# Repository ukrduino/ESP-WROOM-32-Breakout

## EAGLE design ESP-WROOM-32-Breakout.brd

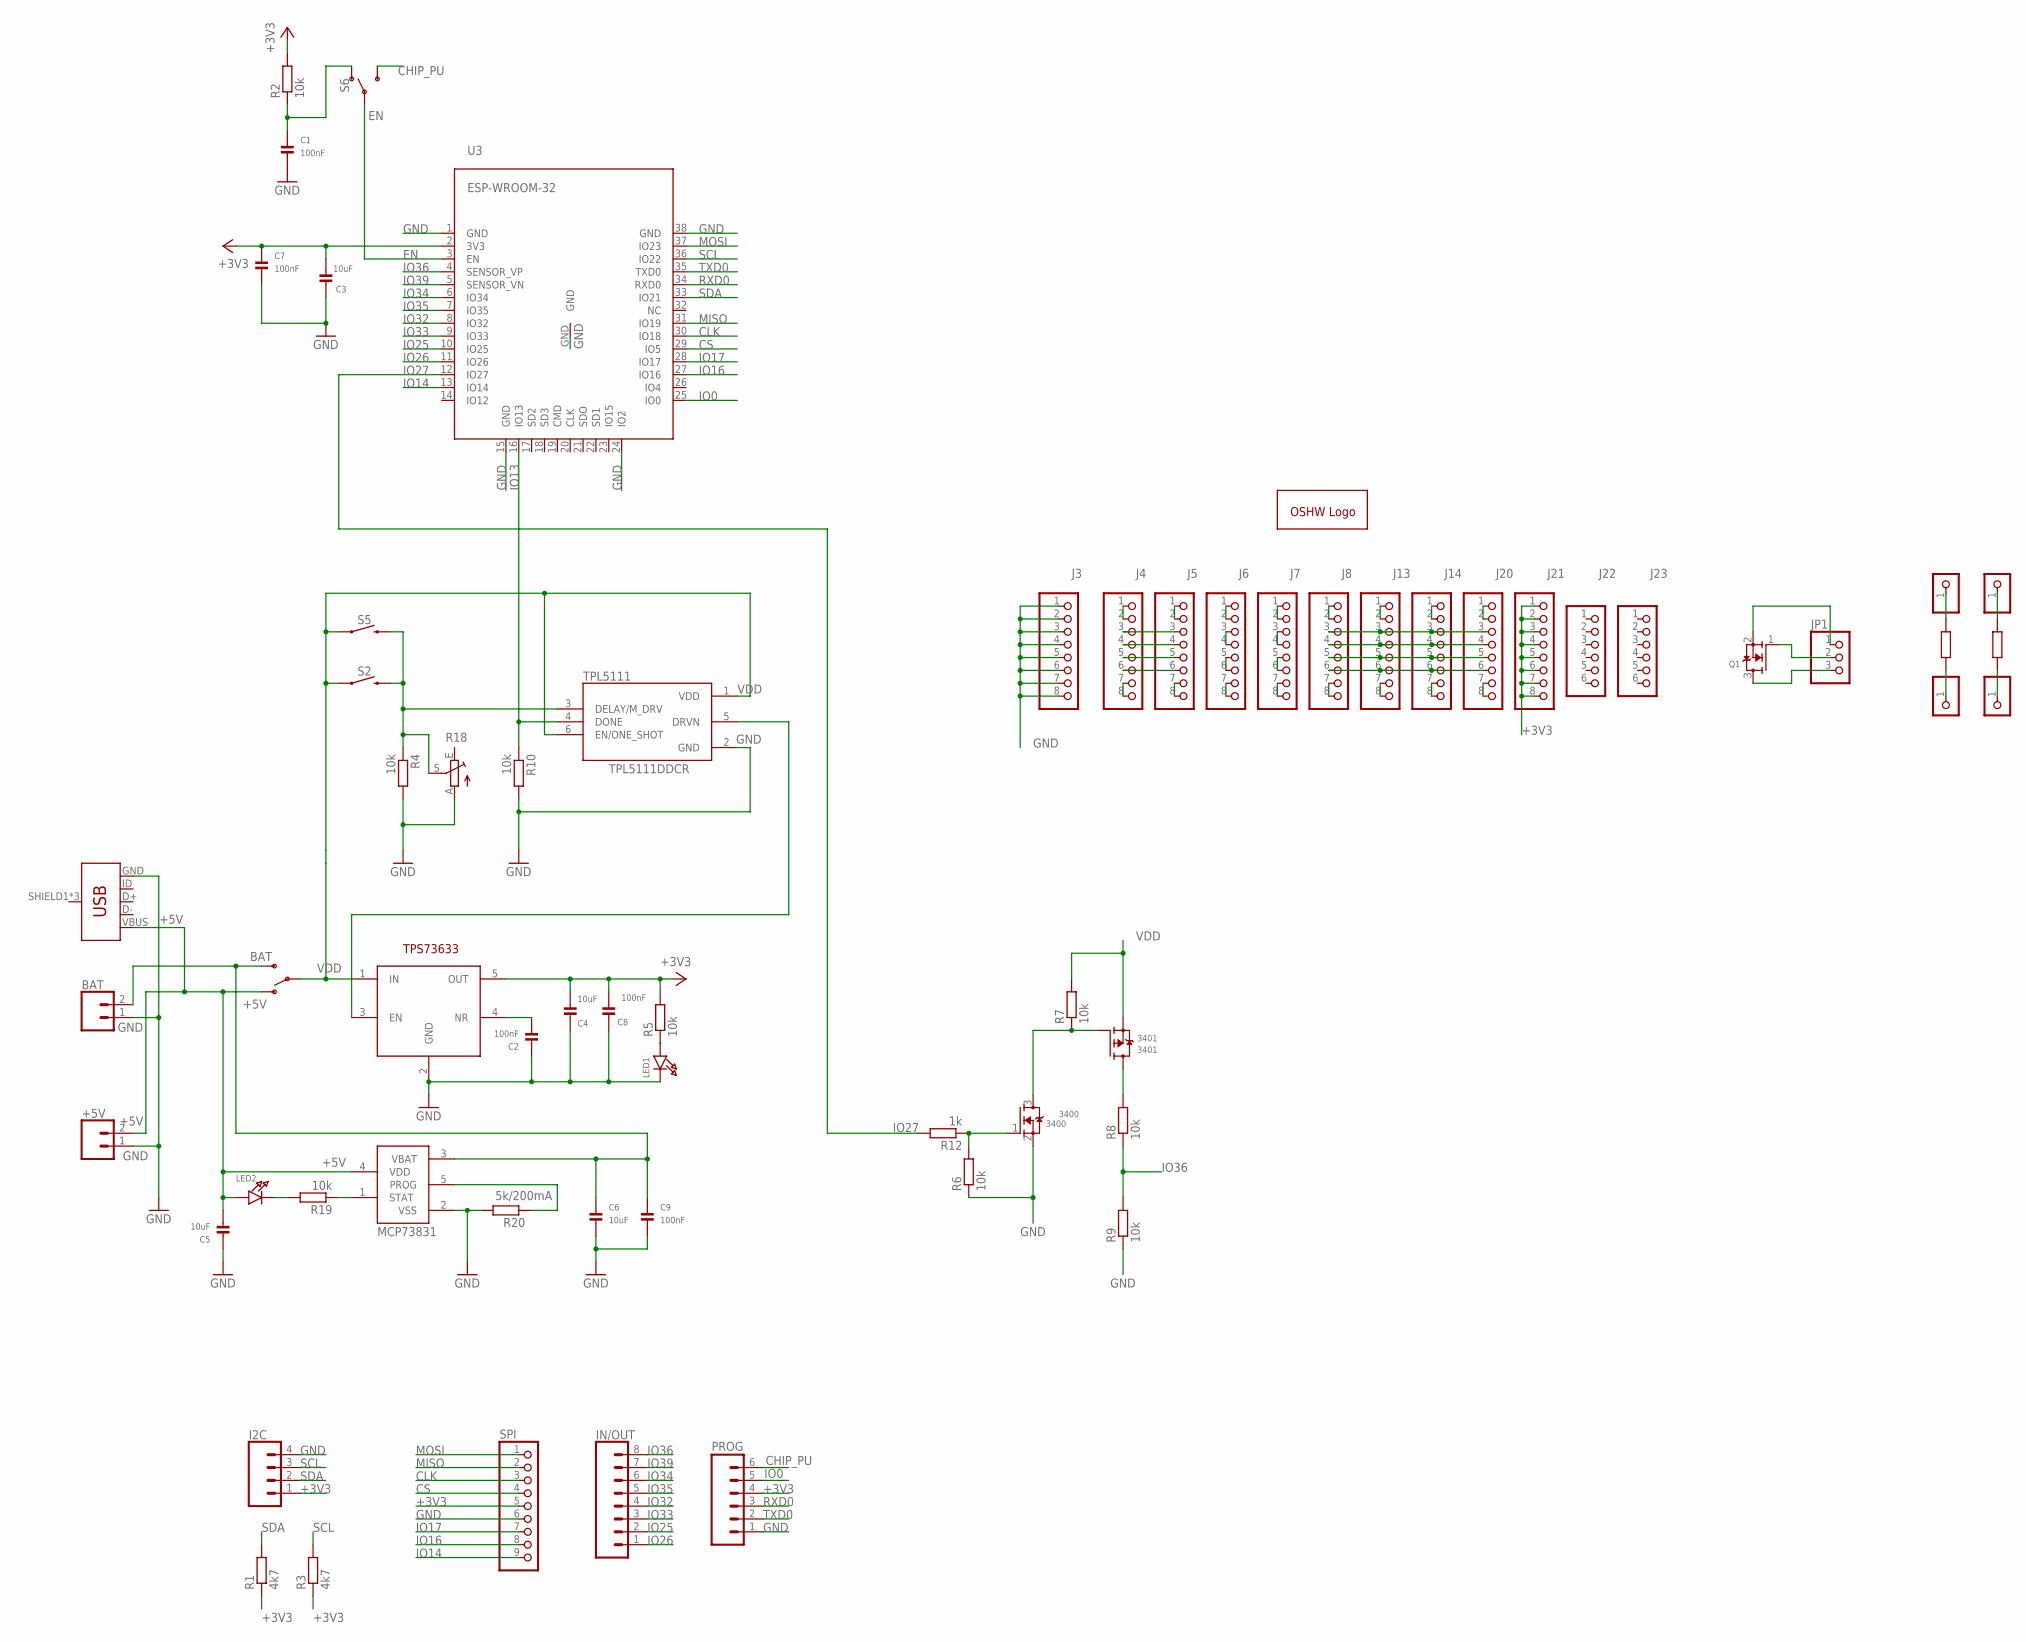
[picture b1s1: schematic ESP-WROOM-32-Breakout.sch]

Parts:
3400: 3400; SOT23-WIDE
3401: 3401; SOT23-WIDE
+5V: CONN_02; 1X02
BAT: CONN_02; 1X02
C1, C2, C7, C8, C9: 100nF; 1206
C3, C4, C5, C6: 10uF; 1206
GOLD_ORB_SM1: OSHWLOGOLOGO8MM; OSHW_8MM
I2C: CONN_041X04_NO_SILK; 1X04_NO_SILK
IN/OUT: CONN_08NO_SILK_FEMALE_PTH; 1X08_NO_SILK
J1: USB_MICRO-B_FEMALE-SMT; USB-B-MICRO-SMD
J3, J4, J5, J6, J7, J8, J13, J14, J20, J21: HEADER-1X8ROUND; 1X08_ROUND
J22, J23: HEADER-1X670MIL; 1X06_ROUND_70
JP1: HEADER-1X376MIL; 1X03_ROUND_76
JP2, JP3, JP4, JP5: HEADER-1X12MM; 1X01_2MM
LED1, LED2: LED1206; CHIPLED_1206
PROG: CONN_06NO_SILK_NO_POP; 1X06_NO_SILK
Q1: MOSFET-NWIDE; SOT23-WIDE
R1, R3: 4k7; R1206
R2, R4, R5, R6, R7, R8, R9, R10, R11, R13, R19: 10k; R1206
R12: 1k; R1206
R18: TRIM_EU-CT6; CT6
R20: 5k/200mA; R1206
S2: MOMENTARY-SWITCH-SPST-SMD-6.2MM-TALL; TACTILE_SWITCH_SMD_6.2MM_TALL
S3, S6: SWITCH-SPDT-PTH-11.6X4.0MM; SWITCH_SPDT_PTH_11.6X4.0MM
S5: MOMENTARY-SWITCH-SPST-PTH-RIGHT-ANGLE-KIT; TACTILE_SWITCH_PTH_RIGHT_ANGLE_KIT
SPI: HEADER-1X970MIL; 1X09_ROUND_70
TPL5111: TPL5111DDCR; SOT95P280X110-6N
TPS73633: TPS73633DBVR; SOT23-DBV
U3: ESP-WROOM-32
U$1: MCP73831; SOT23-5L

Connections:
+3V3: C3.2, C4.2, C7.1, C8.2, I2C.1, J21.1, J21.2, J21.3, J21.4, J21.5, J21.6, J21.7, J21.8, PROG.4, R1.1, R2.2, R3.1, R5.2, SPI.5, TPS73633.5 (OUT), U3.2 (3V3)
+5V: +5V.2, C5.2, J1.VBUS, LED2.A, S3.1 (O), U$1.4 (VDD)
BAT: BAT.2, C6.1, C9.1, S3.3 (S), U$1.3 (VBAT)
CHIP_PU: PROG.6, S6.3 (S)
CLK: SPI.3, U3.30 (IO18)
CS: SPI.4, U3.29 (IO5)
EN: S6.2, U3.3 (EN)
GND: 3400.2 (S), +5V.1, BAT.1, C1.2, C2.1, C3.1, C4.1, C5.1, C6.2, C7.2, C8.1, C9.2, I2C.4, J1.GND, J3.1, J3.2, J3.3, J3.4, J3.5, J3.6, J3.7, J3.8, LED1.C, PROG.1, R4.2, R6.1, R9.1, R10.2, R18.A, R20.2, SPI.6, TPL5111.2 (GND), TPS73633.2 (GND), U3.1 (GND), U3.15 (GND), U3.24 (IO2), U3.38 (GND), U3.GND, U$1.2 (VSS)
IO0: PROG.5, U3.25 (IO0)
IO13: R10.1, TPL5111.4 (DONE), U3.16 (IO13)
IO14: SPI.9, U3.13 (IO14)
IO16: SPI.8, U3.27 (IO16)
IO17: SPI.7, U3.28 (IO17)
IO25: IN/OUT.2, U3.10 (IO25)
IO26: IN/OUT.1, U3.11 (IO26)
IO27: R12.2, U3.12 (IO27)
IO32: IN/OUT.4, U3.8 (IO32)
IO33: IN/OUT.3, U3.9 (IO33)
IO34: IN/OUT.6, U3.6 (IO34)
IO35: IN/OUT.5, U3.7 (IO35)
IO36: IN/OUT.8, R8.1, R9.2, U3.4 (SENSOR_VP)
IO39: IN/OUT.7, U3.5 (SENSOR_VN)
MISO: SPI.2, U3.31 (IO19)
MOSI: SPI.1, U3.37 (IO23)
unnamed: TPL5111.5 (DRVN), TPS73633.3 (EN)
unnamed: JP1.1, Q1.2 (S)
unnamed: C2.2, TPS73633.4 (NR)
unnamed: R4.1, R18.S, S2.B2 (2), S5.2, TPL5111.3 (DELAY/M_DRV)
unnamed: LED1.A, R5.1
unnamed: JP1.2, Q1.1 (G)
unnamed: JP1.3, Q1.3 (D)
unnamed: 3400.3 (D), 3401.1 (G), R7.1
unnamed: JP2.1, R11.2
unnamed: 3401.3 (D), R8.2
unnamed: JP3.1, R11.1
unnamed: JP4.1, R13.2
unnamed: JP5.1, R13.1
unnamed: C1.1, R2.1, S6.1 (O)
unnamed: R19.1, U$1.1 (STAT)
unnamed: 3400.1 (G), R6.2, R12.1
unnamed: J4.1, J4.2
unnamed: J5.1, J5.2
unnamed: J4.3, J5.3
unnamed: J4.4, J5.4
unnamed: J4.5, J5.5
unnamed: J4.6, J5.6
unnamed: J4.7, J4.8
unnamed: J5.7, J5.8
unnamed: J7.1, J7.2
unnamed: J7.3, J7.4
unnamed: J7.5, J7.6
unnamed: J7.7, J7.8
unnamed: J8.7, J8.8
unnamed: R20.1, U$1.5 (PROG)
unnamed: J20.7, J20.8
unnamed: J6.3, J6.4
unnamed: J8.1, J8.2
unnamed: J6.1, J6.2
unnamed: J13.1, J13.2
unnamed: J8.3, J13.3, J14.3, J20.3
unnamed: J8.4, J13.4, J14.4, J20.4
unnamed: J8.5, J13.5, J14.5, J20.5
unnamed: J8.6, J13.6, J14.6, J20.6
unnamed: J6.7, J6.8
unnamed: J13.7, J13.8
unnamed: J14.7, J14.8
unnamed: J14.1, J14.2
unnamed: J20.1, J20.2
unnamed: J6.5, J6.6
unnamed: LED2.C, R19.2
RXD0: PROG.3, U3.34 (RXD0)
SCL: I2C.3, R3.2, U3.36 (IO22)
SDA: I2C.2, R1.2, U3.33 (IO21)
TXD0: PROG.2, U3.35 (TXD0)
VDD: 3401.2 (S), R7.2, S2.A2 (1), S3.2, S5.1, TPL5111.1 (VDD), TPL5111.6 (EN/ONE_SHOT), TPS73633.1 (IN)

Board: 2 copper layers, 63 parts (1 on the bottom side), 75 nets, no tracks yet.

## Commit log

2019-03-15 images added
2019-03-15 readme added
2019-03-15 Photo added to read me
2019-03-15 board added
2019-03-15 Finished layout
2019-03-26 datasheets added
2019-03-26 save

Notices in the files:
parts and their libraries:
microbuilder: This work is placed in the public domain, and may be freely used for commercial and non-commercial work with the following conditions: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
SparkFun-Switches: Licensing: Creative Commons ShareAlike 4.0 International - https://creativecommons.org/licenses/by-sa/4.0
